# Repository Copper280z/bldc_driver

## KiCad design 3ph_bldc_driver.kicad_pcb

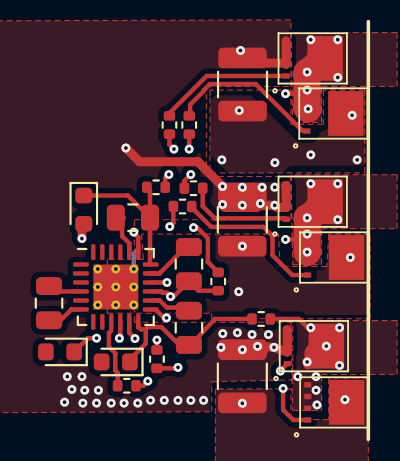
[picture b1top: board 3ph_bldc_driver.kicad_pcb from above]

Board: 4 copper layers, 26 parts (0 on the bottom side), 24 nets.

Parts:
C1, C2, C3: 1u; C_0805_2012Metric
C4: 10u; C_0805_2012Metric
C5, C6, C7: 10u; C_1210_3225Metric
D1, D2, D3: D; D_0603_1608Metric
Q1, Q2, Q3, Q4, Q5, Q6: AON7264E-HXY; DFN3x3-8L
R1, R2, R3, R4, R5, R6, R7, R8, R9: 0R; R_0402_1005Metric
U1: HVQFN-24-1EP_4x4mm_P0.5mm_EP2.5x2.5mm_ThermalVias

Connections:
+12V: C4.1, U1.4 (GVDD)
+BATT: C5.1, C6.1, C7.1, Q1.2 (D), Q3.2 (D), Q5.2 (D)
/inverter/INV_OUT_A: Q1.3 (S), Q2.2 (D), R7.2
/inverter/INV_OUT_B: Q3.3 (S), Q4.2 (D), R8.2
/inverter/INV_OUT_C: Q5.3 (S), Q6.2 (D), R9.2
GND: C4.2, C5.2, C6.2, C7.2, D1.2 (A), D2.2 (A), D3.2 (A), Q2.3 (S), Q4.3 (S), Q6.3 (S), U1.6 (GND), U1.25 (PWRPAD)
unnamed: C1.2, D1.1 (K), R7.1, U1.18 (SHA)
unnamed: C2.2, D2.1 (K), R8.1, U1.15 (SHB)
unnamed: C3.2, D3.1 (K), R9.1, U1.12 (SHC)
unnamed: Q1.1 (G), R1.2
unnamed: Q2.1 (G), R2.2
unnamed: Q3.1 (G), R3.2
unnamed: Q4.1 (G), R4.2
unnamed: Q5.1 (G), R5.2
unnamed: Q6.1 (G), R6.2
unnamed: C1.1, U1.20 (BSTA)
unnamed: C2.1, U1.17 (BSTB)
unnamed: C3.1, U1.14 (BSTC)
unnamed: R1.1, U1.19 (GHA)
unnamed: R3.1, U1.16 (GHB)
unnamed: R5.1, U1.13 (GHC)
unnamed: R2.1, U1.11 (GLA)
unnamed: R4.1, U1.10 (GLB)
unnamed: R6.1, U1.9 (GLC)

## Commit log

2024-02-24 found real parts for capacitors, added 0 ohm resistors, added diode footprints for src line
